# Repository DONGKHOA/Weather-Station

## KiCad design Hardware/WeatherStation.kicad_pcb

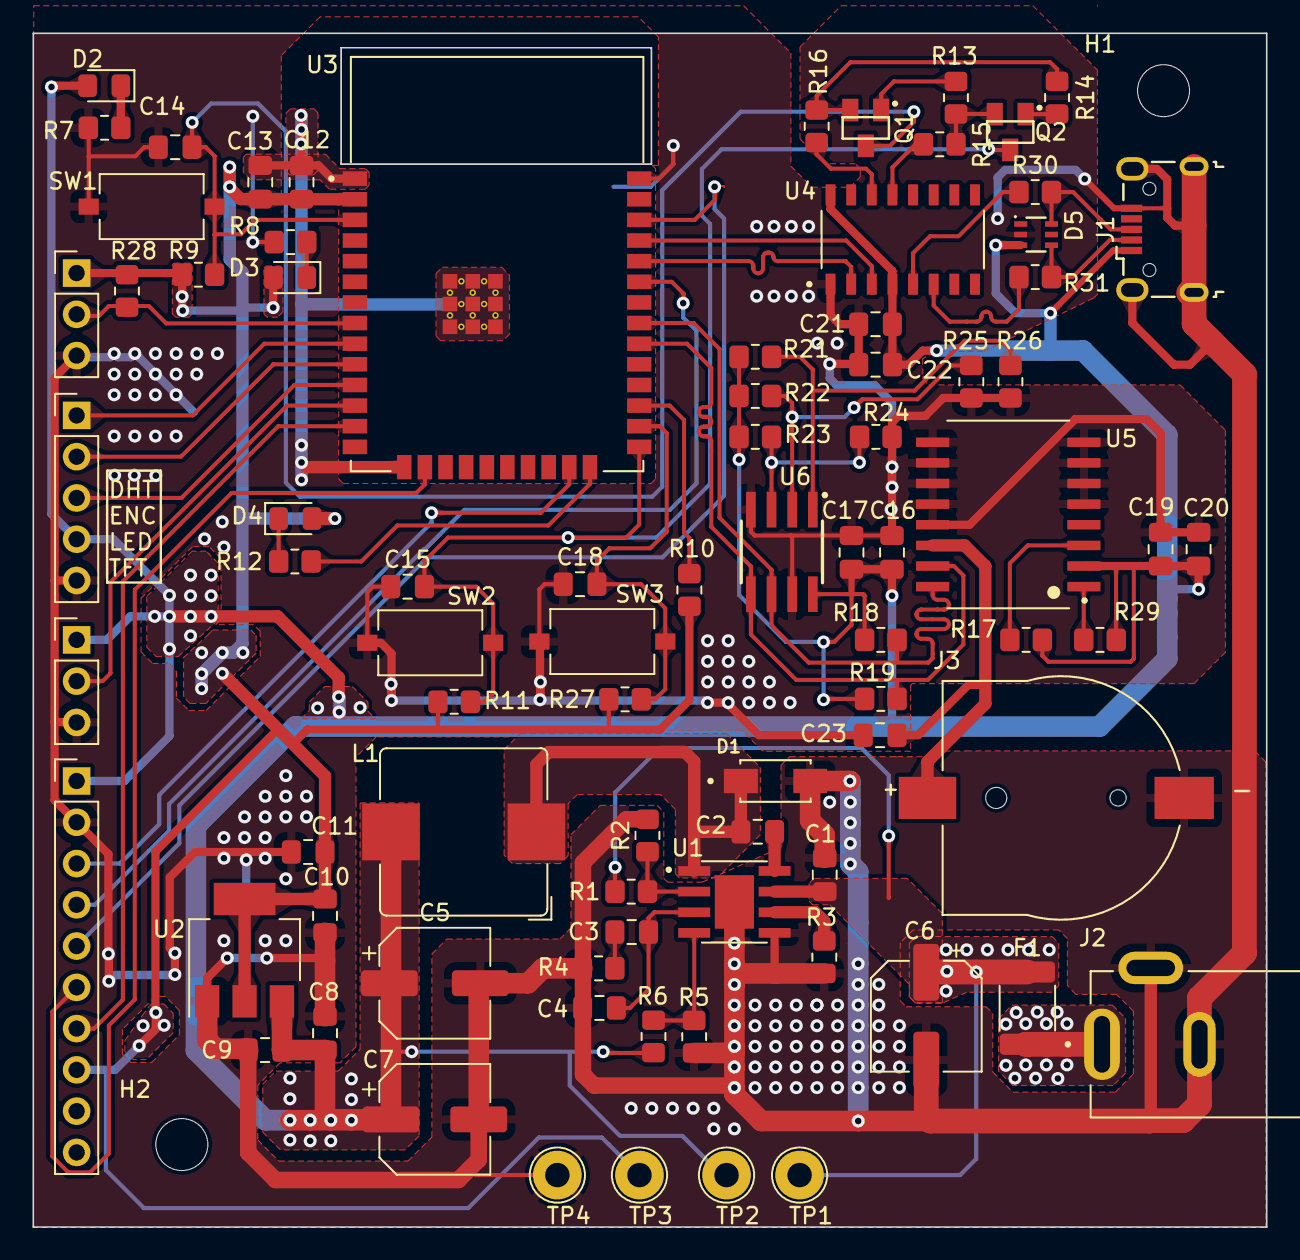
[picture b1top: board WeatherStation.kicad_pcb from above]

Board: 2 copper layers, 75.9 x 73.5 mm, 84 parts (0 on the bottom side), 50 nets.

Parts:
C1: 10uF, 50V; C_0805_2012Metric_Pad1.18x1.45mm_HandSolder
C2, C9, C10, C12, C14, C15, C17, C18, C19, C21: 100nF; C_0805_2012Metric_Pad1.18x1.45mm_HandSolder
C3: 150pF; C_0805_2012Metric_Pad1.18x1.45mm_HandSolder
C4: NS; C_0805_2012Metric_Pad1.18x1.45mm_HandSolder
C5: 22uF; CP_Elec_6.3x5.4
C6, C7: 47uF; CP_Elec_6.3x7.7
C8, C11, C16, C20, C23: 1uF; C_0805_2012Metric_Pad1.18x1.45mm_HandSolder
C13, C22: 22uF; C_0805_2012Metric_Pad1.18x1.45mm_HandSolder
D1: SS34; DIOM4325X250N
D2, D3, D4: LED; LED_0805_2012Metric_Pad1.15x1.40mm_HandSolder
D5: SMF05C; SC70-6
F1: Fuse_Small; Fuse_1812_4532Metric_Pad1.30x3.40mm_HandSolder
H1, H2: MountingHole; MountingHole_3.2mm_M3
J1: USB_B_Micro; USB_Micro-B_Wuerth_629105150521
J2: DC-005-5A-2.0; XKB_DC-005-5A-2.0
J3: BC501SM-TR; MPD_BC501SM-TR
J4, J7: Conn_01x03_Pin; PinHeader_1x03_P2.54mm_Vertical
J5: Conn_01x05_Pin; PinHeader_1x05_P2.54mm_Vertical
J6: Conn_01x10_Pin; PinHeader_1x10_P2.54mm_Vertical
L1: 22uH; L_Bourns_SRP1038C_10.0x10.0mm
Q1, Q2: MMBT2222A; SOT23
R1, R3, R4: 100k; R_0805_2012Metric_Pad1.20x1.40mm_HandSolder
R2: 24.9k; R_0805_2012Metric_Pad1.20x1.40mm_HandSolder
R5: 40.2k; R_0805_2012Metric_Pad1.20x1.40mm_HandSolder
R6: 220k; R_0805_2012Metric_Pad1.20x1.40mm_HandSolder
R7, R9, R10, R11, R13, R14, R27: 10k; R_0805_2012Metric_Pad1.20x1.40mm_HandSolder
R8, R12: 1k; R_0805_2012Metric_Pad1.20x1.40mm_HandSolder
R15, R16: 22; R_0805_2012Metric_Pad1.20x1.40mm_HandSolder
R17, R18, R19, R21, R22, R23, R28, R29: 4.7k; R_0805_2012Metric_Pad1.20x1.40mm_HandSolder
R24, R25, R26, R30, R31: 0; R_0805_2012Metric_Pad1.20x1.40mm_HandSolder
SW1, SW2, SW3: SW_Push; SW_Tactile_SPST_NO_Straight_CK_PTS636Sx25SMTRLFS
TP1, TP2, TP3, TP4: TestPoint; TestPoint_Loop_D2.54mm_Drill1.5mm_Beaded
U1: MP1584EN-LF-Z; SOIC127P600X170-9N
U2: LM1117MP-3.3; SOT-223-3_TabPin2
U3: ESP32-WROOM-32E_(16MB); XCVR_ESP32-WROOM-32E_(16MB)
U4: CH340C; SOIC127P600X180-16N
U5: DS3231SN#; SOIC127P1032X265-16N
U6: CAT24C32WI-GT3; SOIC127P600X175-8N

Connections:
+3V3: C10.2, C11.2, C12.2, C13.2, D3.2 (A), D4.2 (A), J4.1, J6.8, R9.1, R10.2, R11.1, R27.1, R28.1, TP3.1, U2.2 (VO), U3.2 (3V3)
/MCU/BUTTON_CHECK: C18.2, R27.2, SW3.1, U3.26 (IO4)
/MCU/LED: J7.2, U3.12 (IO27)
/MCU/LED_STATUS: R12.2, U3.24 (IO2)
/MCU/ONE_WIRE_DATA: J4.2, R28.2, U3.8 (IO32)
/MCU/Phase_A: J5.1, U3.9 (IO33)
/MCU/Phase_B: J5.2, U3.10 (IO25)
/MCU/SW: J5.3, U3.11 (IO26)
DIR: Q2.2, R13.2, R15.2
D_N: D5.4, J1.2 (D-), R31.2
D_P: D5.6, J1.3 (D+), R30.2
EN: C14.2, Q1.3, R9.2, SW1.1, U3.3 (EN)
Flash: C15.2, Q2.3, R11.2, SW2.1, U3.25 (IO0)
GND: C1.2, C4.1, C5.2, C6.2, C7.2, C8.1, C9.1, C10.1, C11.1, C12.1, C13.1, C14.1, C15.1, C16.1, C17.1, C18.1, C19.1, C20.1, C21.1, C22.1, C23.1, D1.A, D5.2, J1.5 (GND), J1.6 (Shield), J2.2, J2.3, J3.- (NEG), J4.3, J5.5, J6.2, J7.3, R2.2, R3.2, R4.2, R5.2, R7.2, R8.2, R24.2, R25.2, R26.2, SW1.2, SW2.2, SW3.2, TP4.1, U1.5 (GND), U1.9 (EP), U2.1 (GND), U3.1 (GND), U3.15 (GND), U3.38 (GND), U3.39_1 (GND), U3.39_2 (GND), U3.39_3 (GND), U3.39_4 (GND), U3.39_5 (GND), U3.39_6 (GND), U3.39_7 (GND), U3.39_8 (GND), U3.39_9 (GND), U3.39_10, U3.39_11, U3.39_12, U3.39_13, U3.39_14, U3.39_15, U3.39_16, U3.39_17, U3.39_18, U3.39_19, U3.39_20, U3.39_21, U4.1 (GND), U5.5 (NC), U5.6 (NC), U5.7 (NC), U5.8 (NC), U5.9 (NC), U5.10 (NC), U5.11 (NC), U5.12 (NC), U5.13 (GND), U6.4 (VSS), U6.7 (WP)
unnamed: C3.1, R4.1
unnamed: D2.1 (K), R7.1
unnamed: D3.1 (K), R8.1
unnamed: D4.1 (K), R12.1
unnamed: F1.1, J2.1
unnamed: C23.2, J3.+ (POS), U5.14 (VBAT)
unnamed: Q1.1, R13.1
unnamed: Q2.1, R14.1
unnamed: C2.1, U1.8 (BST)
unnamed: C3.2, C4.2, U1.3 (COMP)
unnamed: R1.2, R2.1, U1.2 (EN)
unnamed: R5.1, R6.1, U1.4 (FB)
unnamed: R3.1, U1.6 (FREQ)
unnamed: C2.2, D1.C, L1.1, U1.1 (SW)
unnamed: R10.1, U3.27 (IO16)
unnamed: R30.1, U4.5 (UD+)
unnamed: R31.1, U4.6 (UD-)
unnamed: R15.1, U4.13 (~DTR)
unnamed: R16.1, U4.14 (~RTS)
unnamed: R29.1, U5.1 (32KHZ)
unnamed: R17.1, U5.3 (SQW/~INT)
unnamed: R21.1, R26.1, U6.1 (A0)
unnamed: R22.1, R25.1, U6.2 (A1)
unnamed: R23.1, R24.1, U6.3 (A2)
RTS: Q1.2, R14.2, R16.2
SCL: R18.1, U3.31 (IO19), U5.16 (SCL), U6.6 (SCL)
SDA: R19.1, U3.30 (IO18), U5.15 (SDA), U6.5 (SDA)
SPI_CS: J6.3, U3.23 (IO15)
SPI_MOSI: J6.6, U3.16 (IO13)
SPI_RESET: J6.4, U3.33 (IO21)
SPI_RS: J6.5, U3.36 (IO22)
SPI_SCLK: J6.7, U3.13 (IO14)
U0_N: U3.34 (RXD0), U4.2 (TXD)
U0_P: U3.35 (TXD0), U4.3 (RXD)
V_USB: C5.1, C7.1, C8.2, C9.2, C16.2, C17.2, C19.2, C20.2, C21.2, C22.2, D2.2 (A), D5.3, J1.1 (VBUS), J5.4, J6.1, J7.1, L1.2, R6.2, R17.2, R18.2, R19.2, R21.2, R22.2, R23.2, R29.2, TP2.1, U2.3 (VI), U4.4 (V3), U4.16 (VCC), U5.2 (VCC), U6.8 (VCC)
Vin: C1.1, C6.1, F1.2, R1.1, TP1.1, U1.7 (VIN)

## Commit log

2024-03-28 file:merge firmware and hardware
